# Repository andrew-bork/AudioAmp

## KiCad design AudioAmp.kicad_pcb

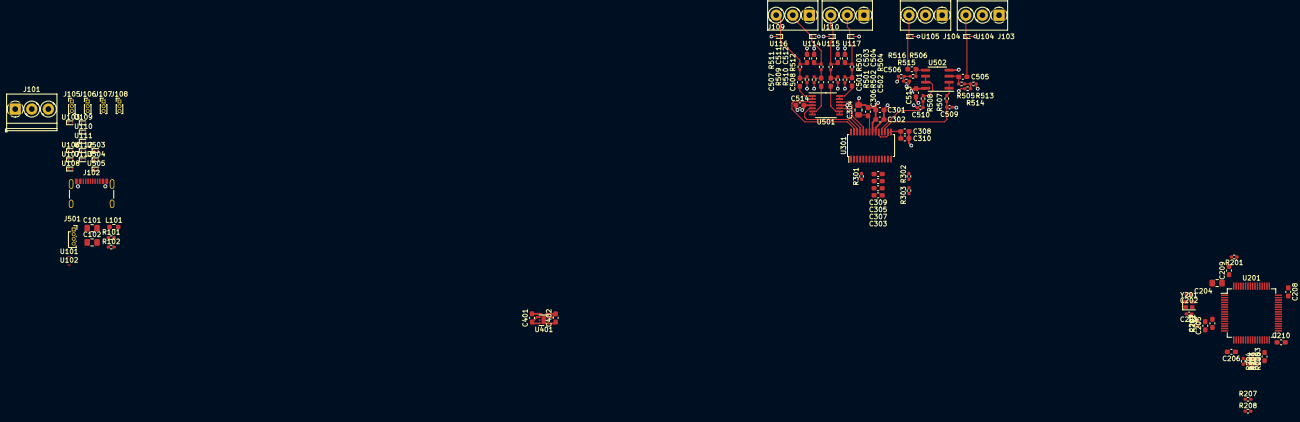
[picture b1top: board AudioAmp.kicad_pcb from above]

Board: 4 copper layers, 105 parts (0 on the bottom side), 61 nets.

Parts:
C101, C102, C204: 4.7u; C_0805_2012Metric_Pad1.18x1.45mm_HandSolder
C201, C202: 19p 1%; C_0402_1005Metric_Pad0.74x0.62mm_HandSolder
C203: 2.2u; C_0603_1608Metric_Pad1.08x0.95mm_HandSolder
C205, C301, C303, C307, C308, C401, C402: 1u; C_0603_1608Metric_Pad1.08x0.95mm_HandSolder
C206, C207, C208, C209, C210, C302, C305, C306, C309, C310, C501, C502, C503, C504, C505, C506, C507, C508, C511, C512, C513, C514: 0.1u; C_0603_1608Metric_Pad1.08x0.95mm_HandSolder
C304: 47u; C_0805_2012Metric_Pad1.18x1.45mm_HandSolder
C509, C510: 1n; C_0402_1005Metric_Pad0.74x0.62mm_HandSolder
J101: Power Terminal; TerminalBlock_Phoenix_PT-1,5-3-3.5-H_1x03_P3.50mm_Horizontal
J102: USB C Port; USB_C_Receptacle_GCT_USB4105-xx-A_16P_TopMnt_Horizontal
J103: Mic 1 Connector; TerminalBlock_Phoenix_PT-1,5-3-3.5-H_1x03_P3.50mm_Horizontal
J104: Mic 2 Connector; TerminalBlock_Phoenix_PT-1,5-3-3.5-H_1x03_P3.50mm_Horizontal
J105: GPIO 0 Connector; PinHeader_1x03_P1.00mm_Vertical
J106: GPIO 1 Connector; PinHeader_1x03_P1.00mm_Vertical
J107: GPIO 2 Connector; PinHeader_1x03_P1.00mm_Vertical
J108: GPIO 3 Connector; PinHeader_1x03_P1.00mm_Vertical
J109: Speaker Right Connector; TerminalBlock_Phoenix_PT-1,5-3-3.5-H_1x03_P3.50mm_Horizontal
J110: Speaker Left Connector; TerminalBlock_Phoenix_PT-1,5-3-3.5-H_1x03_P3.50mm_Horizontal
J501: SWD Connector; PinSocket_1x04_P1.00mm_Vertical
L101: 120 Ohms @ 100 MHz; R_0603_1608Metric_Pad0.98x0.95mm_HandSolder
R101, R102, R201, R202, R207, R208, R302, R303: 10k; R_0402_1005Metric_Pad0.72x0.64mm_HandSolder
R203, R204, R205, R206, R301: 22; R_0402_1005Metric_Pad0.72x0.64mm_HandSolder
R501, R502, R503, R504, R507, R508, R509, R510, R511, R512, R513, R514, R515, R516: 2.2k; R_0402_1005Metric_Pad0.72x0.64mm_HandSolder
R505, R506: 1M; R_0402_1005Metric_Pad0.72x0.64mm_HandSolder
U101, U102: Infineon_SG-WLL-2-3_0.58x0.28_P0.36mm
U103, U104, U105, U106, U107, U108, U109, U110, U111, U112, U113, U114, U115, U116, U117, U503, U504, U505: D_SOD-923
U201: STM32F446RCTx; LQFP-64_10x10mm_P0.5mm
U301: TSSOP-28_4.4x9.7mm_P0.65mm
U401: TLV75733PDRV; WSON-6-1EP_2x2mm_P0.65mm_EP1x1.6mm
U501: TSSOP-14_4.4x5mm_P0.65mm
U502: SOIC-8_3.9x4.9mm_P1.27mm
Y201: Crystal_GND24; Crystal_SMD_2016-4Pin_2.0x1.6mm

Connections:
+3V3: C204.1, C205.1, C206.1, C207.1, C208.1, C209.1, C210.1, C303.1, C305.1, C307.1, C309.1, C402.1, J105.3, J106.3, J107.3, J108.3, R202.1, R207.1, R208.1, U110.1, U111.1, U112.1, U113.1, U201.1 (VBAT), U201.13 (VDDA), U201.19 (VDD), U201.32 (VDD), U201.48 (VDD), U201.64 (VDD), U301.9 (VD), U301.10 (VL), U401.1 (OUT)
+5V: C102.2, C301.1, C302.1, C401.1, C513.1, C514.2, L101.2, R513.1, R515.1, U301.20 (VA), U401.4 (EN), U401.6 (IN), U501.4 (V+), U502.8 (V+)
/Codec/CODEC_CS: R303.1, U301.13 (AD0/~CS(I2S/~LJ))
/Codec/FILT: C304.1, C306.1, U301.22 (FILT+)
/Codec/codec_sdout_sereis: R301.2, U301.6 (SDOUT(M/~S))
/Connectors/5V_INPUT: C101.2, J101.3, L101.1
/Connectors/VBUS_USB: J102.A4 (VBUS), J102.A9 (VBUS), J102.B4 (VBUS), J102.B9 (VBUS), R101.1, U103.1
/MCU/VCAP_1: C203.1, U201.30 (VCAP_1)
/MCU/crystal_A: C202.1, U201.5 (PH0), Y201.3
/MCU/crystal_B: C201.1, U201.6 (PH1), Y201.1
/MCU/i2s_1_sd_sereis: R206.1, U201.23 (PA7)
/MCU/i2s_clk_series: R205.1, U201.21 (PA5)
/MCU/i2s_mclk_series: R203.2, U201.24 (PC4)
/MCU/i2s_ws _series: R204.1, U201.20 (PA4)
CODEC_RST: R302.1, U201.62 (PB9), U301.14 (~RST)
GND: C101.1, C102.1, C201.2, C202.2, C203.2, C204.2, C205.2, C206.2, C207.2, C208.2, C209.2, C210.2, C301.2, C302.2, C303.2, C304.2, C305.2, C306.2, C307.2, C308.2, C309.2, C310.2, C401.2, C402.2, C503.1, C504.1, C509.1, C510.1, C511.1, C512.1, C513.2, C514.1, J101.1, J102.A1 (GND), J102.A12 (GND), J102.B1 (GND), J102.B12 (GND), J103.2, J104.2, J105.1, J106.1, J107.1, J108.1, J109.1, J110.1, J501.1, R102.2, R201.2, R302.2, R303.2, R501.2, R502.2, R509.2, R510.2, R514.2, R516.2, U101.2, U102.2, U103.2, U104.2, U105.2, U106.2, U107.2, U108.2, U109.1, U110.2, U111.2, U112.2, U113.2, U114.2, U115.2, U116.2, U117.2, U201.12 (VSSA), U201.18 (VSS), U201.31 (VSS), U201.47 (VSS), U201.63 (VSS), U301.8 (DGND), U301.21 (AGND), U401.3 (GND), U401.7 (GND), U501.11 (V-), U502.4 (V-), U503.2, U504.2, U505.2, Y201.2, Y201.4
GNDS: R505.1, R506.1, R513.2, R514.1, R515.2, R516.1
GPIO_A0: J105.2, U106.1, U201.37 (PC6)
GPIO_A1: J106.2, U107.1, U201.38 (PC7)
GPIO_A2: J107.2, U108.1, U201.39 (PC8)
GPIO_A3: J108.2, U109.2, U201.40 (PC9)
I2C_1_SCL: R207.2, U201.58 (PB6), U301.11 (SCL/CCLK(M0))
I2C_1_SDA: R208.2, U201.59 (PB7), U301.12 (SDA/CDIN(M1))
I2S_1_SD: R206.2, U301.7 (SDIN)
I2S_2_SD: R301.1, U201.26 (PB0)
I2S_CLK: R205.2, U201.50 (PA15), U201.51 (PC10), U301.5 (SCLK)
I2S_MCLK: R203.1, U301.3 (MCLK)
I2S_WS: R204.2, U301.4 (LRCK)
MCU_SWCLK: J501.3, U201.49 (PA14), U504.1
MCU_SWDIO: J501.2, U201.46 (PA13), U503.1
MIC_1_IN: C505.1, J103.3, U104.1
MIC_1_IN_BUF: C509.2, R507.1, U301.17 (AINA)
MIC_2_IN: C506.1, J104.3, U105.1
MIC_2_IN_BUF: C510.2, R508.1, U301.18 (AINB)
unnamed: C501.2, R501.1, R503.1
unnamed: C502.2, R502.1, R504.1
unnamed: C507.2, R509.1, R511.1
unnamed: C508.2, R510.1, R512.1
unnamed: R201.1, U201.60 (BOOT0)
unnamed: R202.2, U201.7 (NRST)
unnamed: C507.1, U501.1, U501.2 (-)
unnamed: C508.1, U501.6 (-), U501.7
unnamed: C501.1, U501.8, U501.9 (-)
unnamed: C502.1, U501.13 (-), U501.14
unnamed: C505.2, R505.2, U502.3 (+)
unnamed: R507.2, U502.1, U502.2 (-)
unnamed: C506.2, R506.2, U502.5 (+)
unnamed: R508.2, U502.6 (-), U502.7
RST: J501.4, U505.1
SPKR_LEFT_N: U301.24 (AOUTA-), U501.12 (+)
SPKR_LEFT_N_BUF: C504.2, J110.2, R504.2, U117.1
SPKR_LEFT_P: U301.25 (AOUTA+), U501.10 (+)
SPKR_LEFT_P_BUF: C503.2, J110.3, R503.2, U115.1
SPKR_RIGHT_N: U301.26 (AOUTB+), U501.5 (+)
SPKR_RIGHT_N_BUF: C512.2, J109.2, R512.2, U114.1
SPKR_RIGHT_P: U301.27 (AOUTB-), U501.3 (+)
SPKR_RIGHT_P_BUF: C511.2, J109.3, R511.2, U116.1
USB_D+: J102.A6 (D+), J102.B6 (D+), U101.1
USB_D-: J102.A7 (D-), J102.B7 (D-), U102.1
VBUS_SENSE: R101.2, R102.1, U201.42 (PA9)
VREF: C308.1, C310.1, U301.15 (VQ1), U301.16 (VQ2), U301.19 (VQ3)

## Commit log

2024-06-05 Removed backups from repo
2024-06-05 Add STM project file
2024-06-14 ara ara
